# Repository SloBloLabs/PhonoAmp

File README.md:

# Phono Amp

Phono Amp is a RIAA compliant pre-amplifier circuit that I built into my good old Dual 626, because my living room receiver does not provide phono level inputs.

It is a very simple and straighforward design. Using KiCad simulator, component values were optimized to preserve both a nice bottom end and brilliant treble on the output.

All simulation files are contained and available in this repository.

## Small Signal Analysis from KiCad simulation

## The final product mounted inside the Dual 626 turntable casing

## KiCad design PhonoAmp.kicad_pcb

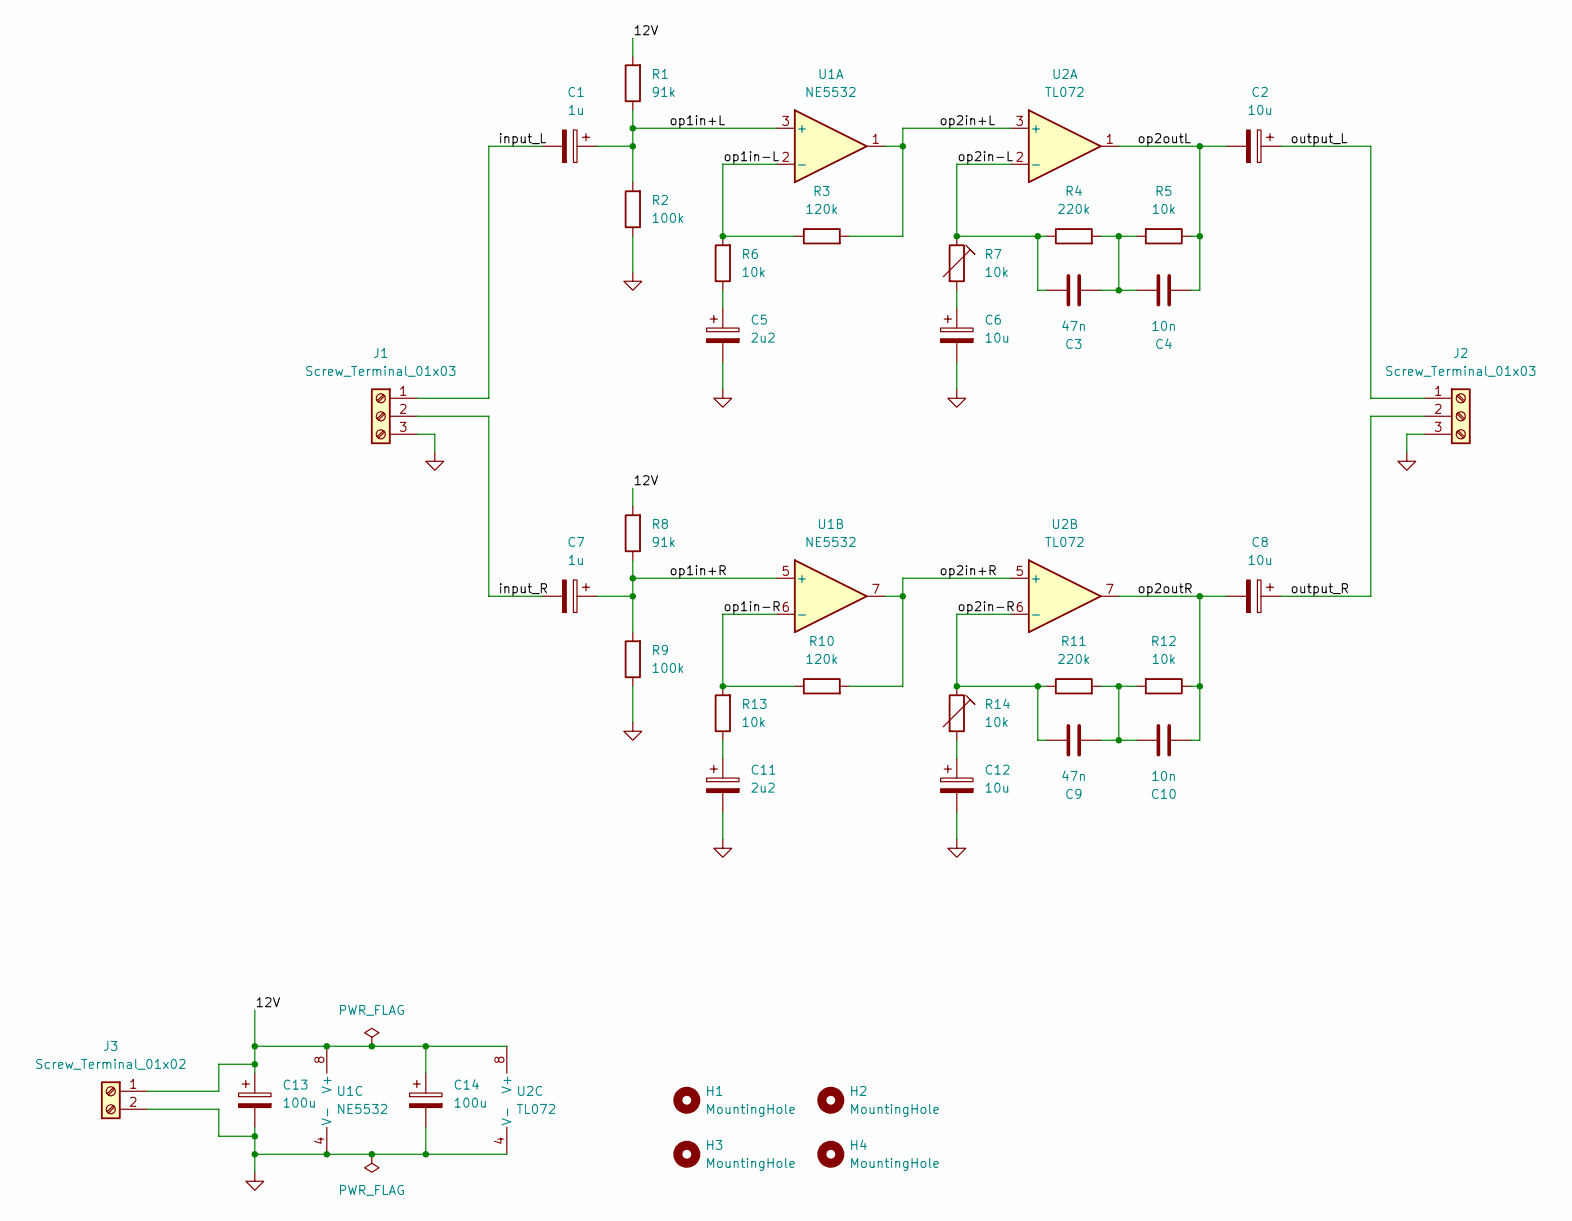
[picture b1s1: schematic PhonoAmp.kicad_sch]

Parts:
C1, C7: 1u; C_Rect_L7.2mm_W5.5mm_P5.00mm_FKS2_FKP2_MKS2_MKP2
C2, C6, C8, C12: 10u; CP_Radial_D5.0mm_P2.00mm
C3, C9: 47n; C_Rect_L7.2mm_W2.5mm_P5.00mm_FKS2_FKP2_MKS2_MKP2
C4, C10: 10n; C_Rect_L7.2mm_W2.5mm_P5.00mm_FKS2_FKP2_MKS2_MKP2
C5, C11: 2u2; CP_Radial_D5.0mm_P2.00mm
C13, C14: 100u; CP_Radial_D8.0mm_P3.50mm
H1, H2, H3, H4: MountingHole; MountingHole_3mm
J1, J2: Screw_Terminal_01x03; PinHeader_1x03_P2.54mm_Vertical
J3: Screw_Terminal_01x02; PinHeader_1x02_P2.54mm_Vertical
R1, R8: 91k; R_Axial_DIN0207_L6.3mm_D2.5mm_P7.62mm_Horizontal
R2, R9: 100k; R_Axial_DIN0207_L6.3mm_D2.5mm_P7.62mm_Horizontal
R3, R10: 120k; R_Axial_DIN0207_L6.3mm_D2.5mm_P7.62mm_Horizontal
R4, R11: 220k; R_Axial_DIN0207_L6.3mm_D2.5mm_P7.62mm_Horizontal
R5, R6, R12, R13: 10k; R_Axial_DIN0207_L6.3mm_D2.5mm_P7.62mm_Horizontal
R7, R14: 10k; Potentiometer_Bourns_3296W_Vertical
U1: NE5532; DIP-8_W7.62mm_Socket_LongPads
U2: TL072; DIP-8_W7.62mm_Socket_LongPads

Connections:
/12V: C13.1, C14.1, J3.1, R1.2, R8.2, U1.8 (V+), U2.8 (V+)
/input_L: C1.2, J1.1
/input_R: C7.2, J1.2
/op1in+L: C1.1, R1.1, R2.2, U1.3 (+)
/op1in+R: C7.1, R8.1, R9.2, U1.5 (+)
/op1in-L: R3.1, R6.2, U1.2 (-)
/op1in-R: R10.1, R13.2, U1.6 (-)
/op2in+L: R3.2, U1.1, U2.3 (+)
/op2in+R: R10.2, U1.7, U2.5 (+)
/op2in-L: C3.2, R4.1, R7.1, U2.2 (-)
/op2in-R: C9.2, R11.1, R14.1, U2.6 (-)
/op2outL: C2.2, C4.1, R5.1, U2.1
/op2outR: C8.2, C10.1, R12.1, U2.7
/output_L: C2.1, J2.1
/output_R: C8.1, J2.2
GND: C5.2, C6.2, C11.2, C12.2, C13.2, C14.2, J1.3, J2.3, J3.2, R2.1, R9.1, U1.4 (V-), U2.4 (V-)
unnamed: C3.1, C4.2, R4.2, R5.2
unnamed: C5.1, R6.1
unnamed: C6.1, R7.2
unnamed: C9.1, C10.2, R11.2, R12.2
unnamed: C11.1, R13.1
unnamed: C12.1, R14.2

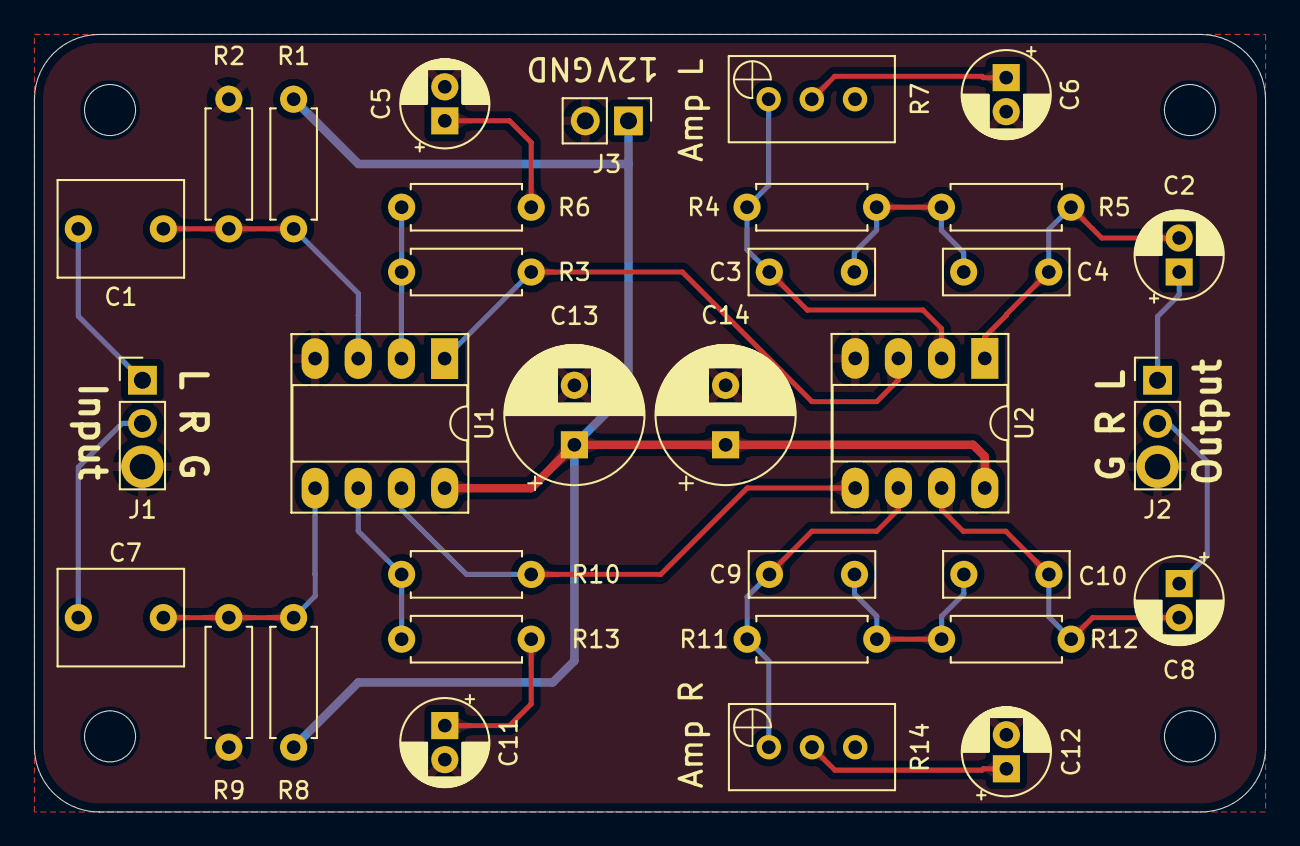
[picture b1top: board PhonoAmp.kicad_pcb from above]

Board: 2 copper layers, 72.4 x 45.7 mm, 37 parts (0 on the bottom side), 22 nets.

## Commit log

2024-07-15 initial commit with simulation
2024-07-16 Component Layout reviewed
2024-07-16 iBom Production files Transferfunctions
2024-07-17 Ordered Version 0v01 Rounded version in separate file Mounting holes aligned with Dual 626 chassis Optimized power supply tracks
2024-07-26 Simulation and Optimization
2024-09-05 Add images from the pcb built in
